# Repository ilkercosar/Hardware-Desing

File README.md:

# Future Hardware-Desing
- 4-6 layer mipi csi to serializer board
- Usb camera controler board
- Luckfox Pico RV1103 I/0 board

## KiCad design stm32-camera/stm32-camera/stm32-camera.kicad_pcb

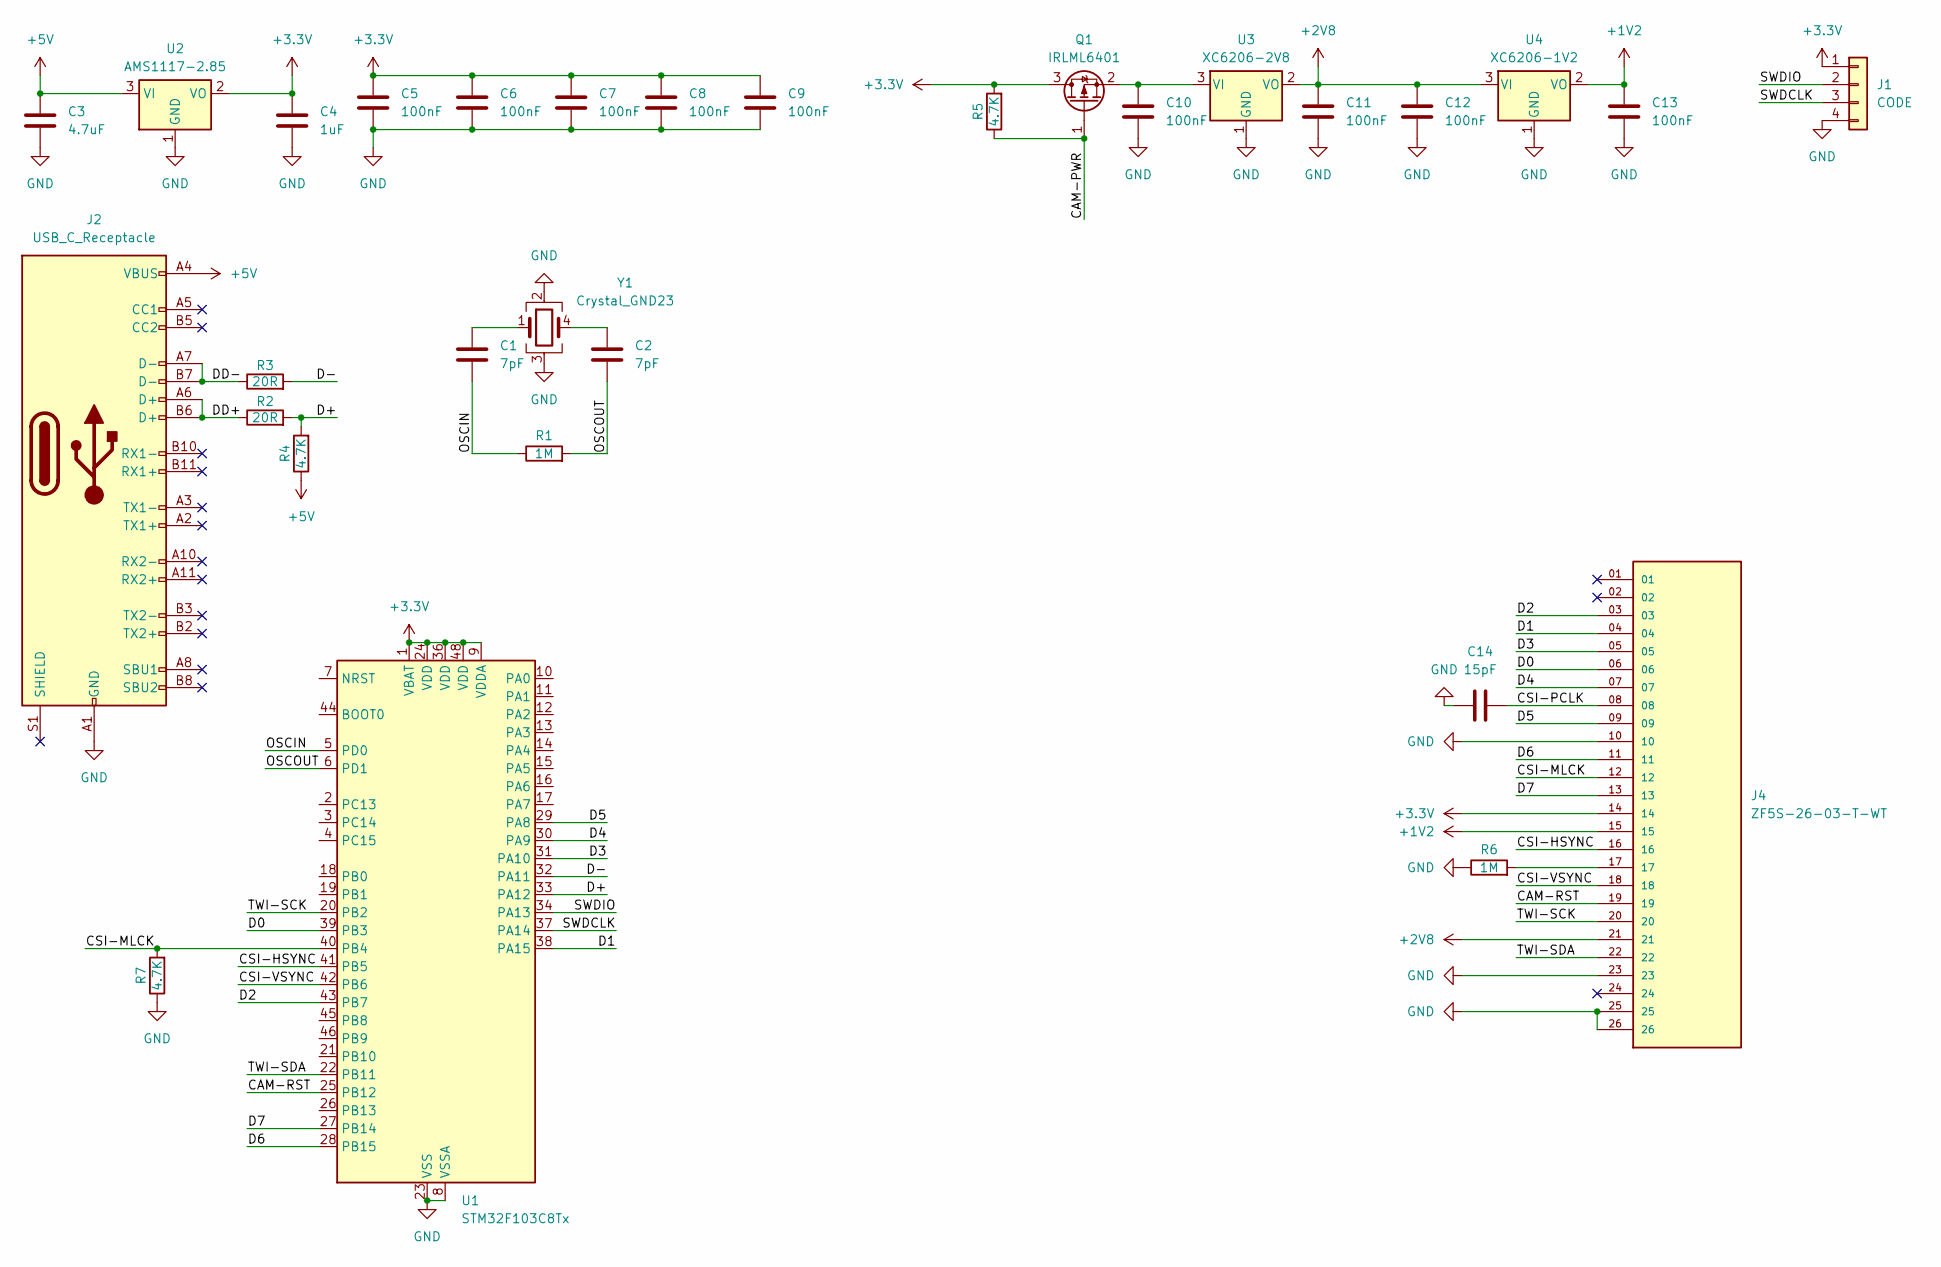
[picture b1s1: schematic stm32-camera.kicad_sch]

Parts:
C1, C2: 7pF; C_0402_1005Metric
C3: 4.7uF; C_0402_1005Metric
C4: 1uF; C_0402_1005Metric
C5, C6, C7, C8, C9, C10, C11, C12, C13: 100nF; C_0402_1005Metric
C14: 15pF; C_0402_1005Metric
J1: CODE; PinHeader_1x04_P2.54mm_Vertical
J2: USB_C_Receptacle; USB_C_Receptacle_JAE_DX07S024WJ3R400
J4: ZF5S-26-03-T-WT; SAMTEC_ZF5S-26-03-T-WT
Q1: IRLML6401; SOT-23
R1, R6: 1M; R_0402_1005Metric
R2, R3: 20R; R_0402_1005Metric
R4, R5, R7: 4.7K; R_0402_1005Metric
U1: STM32F103C8Tx; LQFP-48_7x7mm_P0.5mm
U2: AMS1117-2.85; SOT-223-3_TabPin2
U3: XC6206-2V8; SOT-23-3
U4: XC6206-1V2; SOT-23-3
Y1: Crystal_GND23; Crystal_SMD_SeikoEpson_FA128-4Pin_2.0x1.6mm

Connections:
+1V2: C13.1, J4.15, U4.2 (VO)
+2V8: C11.1, C12.1, J4.21, U3.2 (VO), U4.3 (VI)
+3.3V: C4.1, C5.1, C6.1, C7.1, C8.1, C9.1, J1.1, J4.14, Q1.3 (D), R5.2, U1.1 (VBAT), U1.9 (VDDA), U1.24 (VDD), U1.36 (VDD), U1.48 (VDD), U2.2 (VO)
+5V: C3.1, J2.A4 (VBUS), J2.A9 (VBUS), J2.B4 (VBUS), J2.B9 (VBUS), R4.1, U2.3 (VI)
/CAM-PWR: Q1.1 (G), R5.1
/CAM-RST: J4.19, U1.25 (PB12)
/CSI-HSYNC: J4.16, U1.41 (PB5)
/CSI-MLCK: J4.12, R7.2, U1.40 (PB4)
/CSI-PCLK: C14.2, J4.08
/CSI-VSYNC: J4.18, U1.42 (PB6)
/D0: J4.06, U1.39 (PB3)
/D1: J4.04, U1.38 (PA15)
/D2: J4.03, U1.43 (PB7)
/D3: J4.05, U1.31 (PA10)
/D4: J4.07, U1.30 (PA9)
/D5: J4.09, U1.29 (PA8)
/D6: J4.11, U1.28 (PB15)
/D7: J4.13, U1.27 (PB14)
/D+: R2.2, R4.2, U1.33 (PA12)
/D-: R3.2, U1.32 (PA11)
/DD+: J2.A6 (D+), J2.B6 (D+), R2.1
/DD-: J2.A7 (D-), J2.B7 (D-), R3.1
/OSCIN: C1.2, R1.1, U1.5 (PD0)
/OSCOUT: C2.2, R1.2, U1.6 (PD1)
/SWDCLK: J1.3, U1.37 (PA14)
/SWDIO: J1.2, U1.34 (PA13)
/TWI-SCK: J4.20, U1.20 (PB2)
/TWI-SDA: J4.22, U1.22 (PB11)
GND: C3.2, C4.2, C5.2, C6.2, C7.2, C8.2, C9.2, C10.2, C11.2, C12.2, C13.2, C14.1, J1.4, J2.A1 (GND), J2.A12 (GND), J2.B1 (GND), J2.B12 (GND), J4.10, J4.23, J4.25, J4.26, R6.1, R7.1, U1.8 (VSSA), U1.23 (VSS), U1.35 (VSS), U1.47 (VSS), U2.1 (GND), U3.1 (GND), U4.1 (GND), Y1.2, Y1.3
unnamed: C1.1, Y1.1
unnamed: C2.1, Y1.4
unnamed: J4.17, R6.2
unnamed: C10.1, Q1.2 (S), U3.3 (VI)

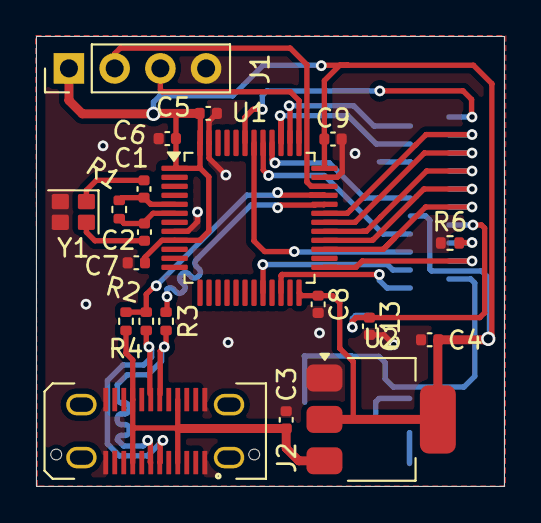
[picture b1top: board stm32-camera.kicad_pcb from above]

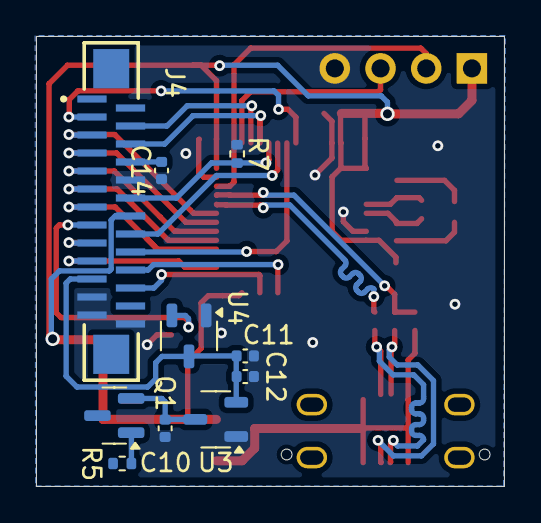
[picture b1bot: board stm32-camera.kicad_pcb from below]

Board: 2 copper layers, 26.0 x 25.0 mm, 30 parts (10 on the bottom side), 33 nets.

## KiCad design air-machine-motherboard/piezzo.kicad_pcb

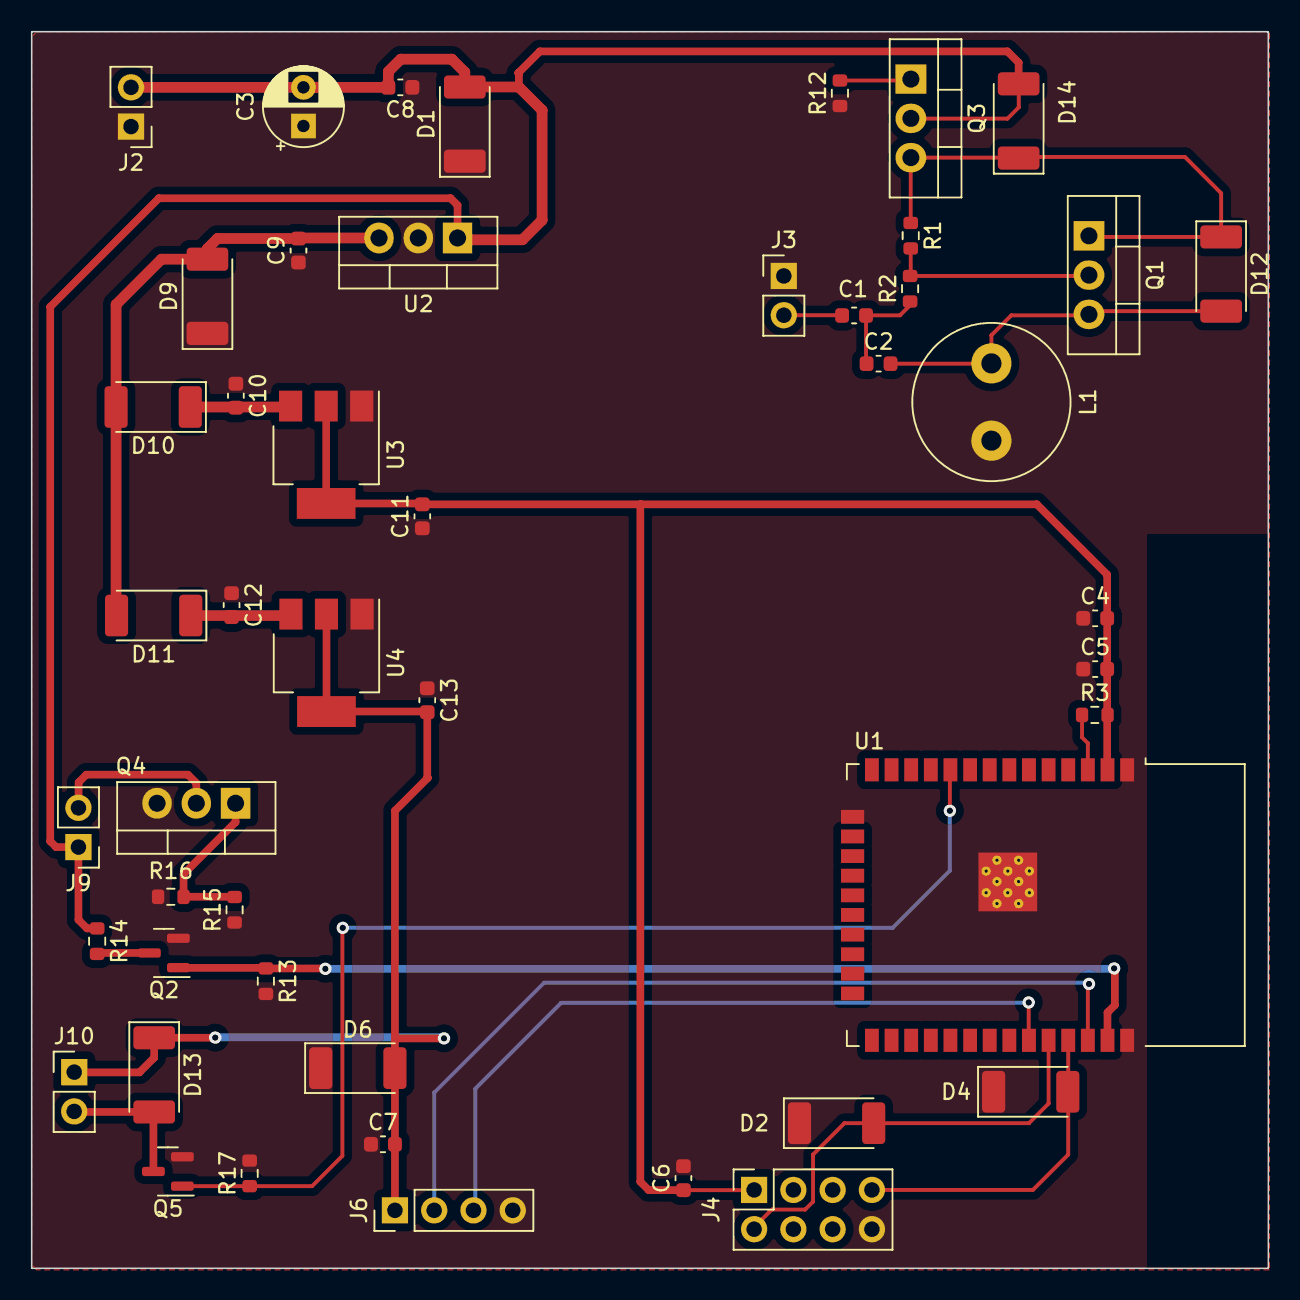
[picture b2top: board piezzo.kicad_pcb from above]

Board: 2 copper layers, 80.0 x 80.0 mm, 48 parts (0 on the bottom side), 24 nets.

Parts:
C1, C5: 1uF; C_0603_1608Metric
C2: 47uH; C_0603_1608Metric
C3: 47uH; CP_Radial_D5.0mm_P2.50mm
C4, C10, C12: 10uF; C_0603_1608Metric
C6, C7: 100nF; C_0603_1608Metric
C8, C9: 330nF; C_0603_1608Metric
C11, C13: 4.7uF; C_0603_1608Metric
D1, D9: SMBJ30CA; D_MELF
D2, D4, D6: SMAJ10CA; D_MELF
D10, D11: RS1M; D_MELF
D12, D13, D14: RS1A; D_MELF
J2, J3: OUT; PinHeader_1x02_P2.54mm_Vertical
J4: CODE; PinSocket_2x04_P2.54mm_Vertical
J6: LCD; PinHeader_1x04_P2.54mm_Vertical
J9: LED; PinHeader_1x02_P2.54mm_Vertical
J10: MOTOR; PinHeader_1x02_P2.54mm_Vertical
L1: 220uH; L_Radial_D10.0mm_P5.00mm_Fastron_07M
Q1: BU407; TO-220-3_Vertical
Q2, Q5: 2N7002; SOT-23
Q3: IRF9540N; TO-220-3_Vertical
Q4: IRF540N; TO-220-3_Vertical
R1, R2: 2.2K; R_0603_1608Metric
R3: 10K; R_0603_1608Metric
R12, R13, R16, R17: 47K; R_0603_1608Metric
R14: 4.7K; R_0603_1608Metric
R15: 1K; R_0603_1608Metric
U1: ESP32-WROOM-32D
U2: LM7812_TO220; TO-220-3_Vertical
U3, U4: AMS1117-3.3; SOT-223-3_TabPin2

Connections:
+3.3V: C4.2, C5.2, C6.1, C7.2, C11.2, C13.2, D6.2 (A2), D13.1 (K), J4.1, J6.1, J10.1, R3.2, U1.2 (VDD), U3.2 (VO), U4.2 (VO)
+12V: C9.2, D9.2 (A2), D10.2 (A), D11.2 (A), U2.3 (VO)
+24V: C3.2, C8.2, D1.2 (A2), D14.2 (A), J2.2, J9.1, Q3.2 (D), R14.1, U2.1 (VI)
/mcu-line/IO0: J4.4, U1.25 (IO0)
/mcu-line/RX: D2.2 (A2), J4.2, U1.34 (RXD0/IO3)
/mcu-line/TX: D4.2 (A2), J4.7, U1.35 (TXD0/IO1)
/piezzo-line/PIEZZO+: C1.2, J3.2
G: Q3.1 (G), R12.2, U1.28 (IO17)
GND: C3.1, C4.1, C5.1, C6.2, C7.1, C8.1, C9.1, C10.1, C11.1, C12.1, C13.1, D1.1 (A1), D2.1 (A1), D4.1 (A1), D6.1 (A1), D9.1 (A1), J2.1, J3.1, J4.8, J6.4, L1.2, Q2.2 (S), Q4.3 (S), Q5.2 (S), R12.1, R13.2, R15.1, R16.2, R17.2, U1.1 (GND), U1.15 (GND), U1.38 (GND), U1.39 (GND), U2.2 (GND), U3.1 (GND), U4.1 (GND)
LED: Q2.1 (G), R13.1, U1.37 (IO23)
MOTOR-SG: Q5.1 (G), R17.1, U1.10 (IO25)
unnamed: C1.1, C2.1, R2.1
unnamed: C10.2, D10.1 (K), U3.3 (VI)
unnamed: C12.2, D11.1 (K), U4.3 (VI)
unnamed: C2.2, D12.2 (A), L1.1, Q1.3 (E)
unnamed: D12.1 (K), D14.1 (K), Q1.1 (C), Q3.3 (S), R1.1
unnamed: D13.2 (A), J10.2, Q5.3 (D)
unnamed: J9.2, Q4.2 (D)
unnamed: Q1.2 (B), R1.2, R2.2
unnamed: Q2.3 (D), R14.2
unnamed: Q4.1 (G), R15.2, R16.1
unnamed: R3.1, U1.3 (EN)
SCL: J6.2, U1.36 (IO22)
SDA: J6.3, U1.33 (IO21)

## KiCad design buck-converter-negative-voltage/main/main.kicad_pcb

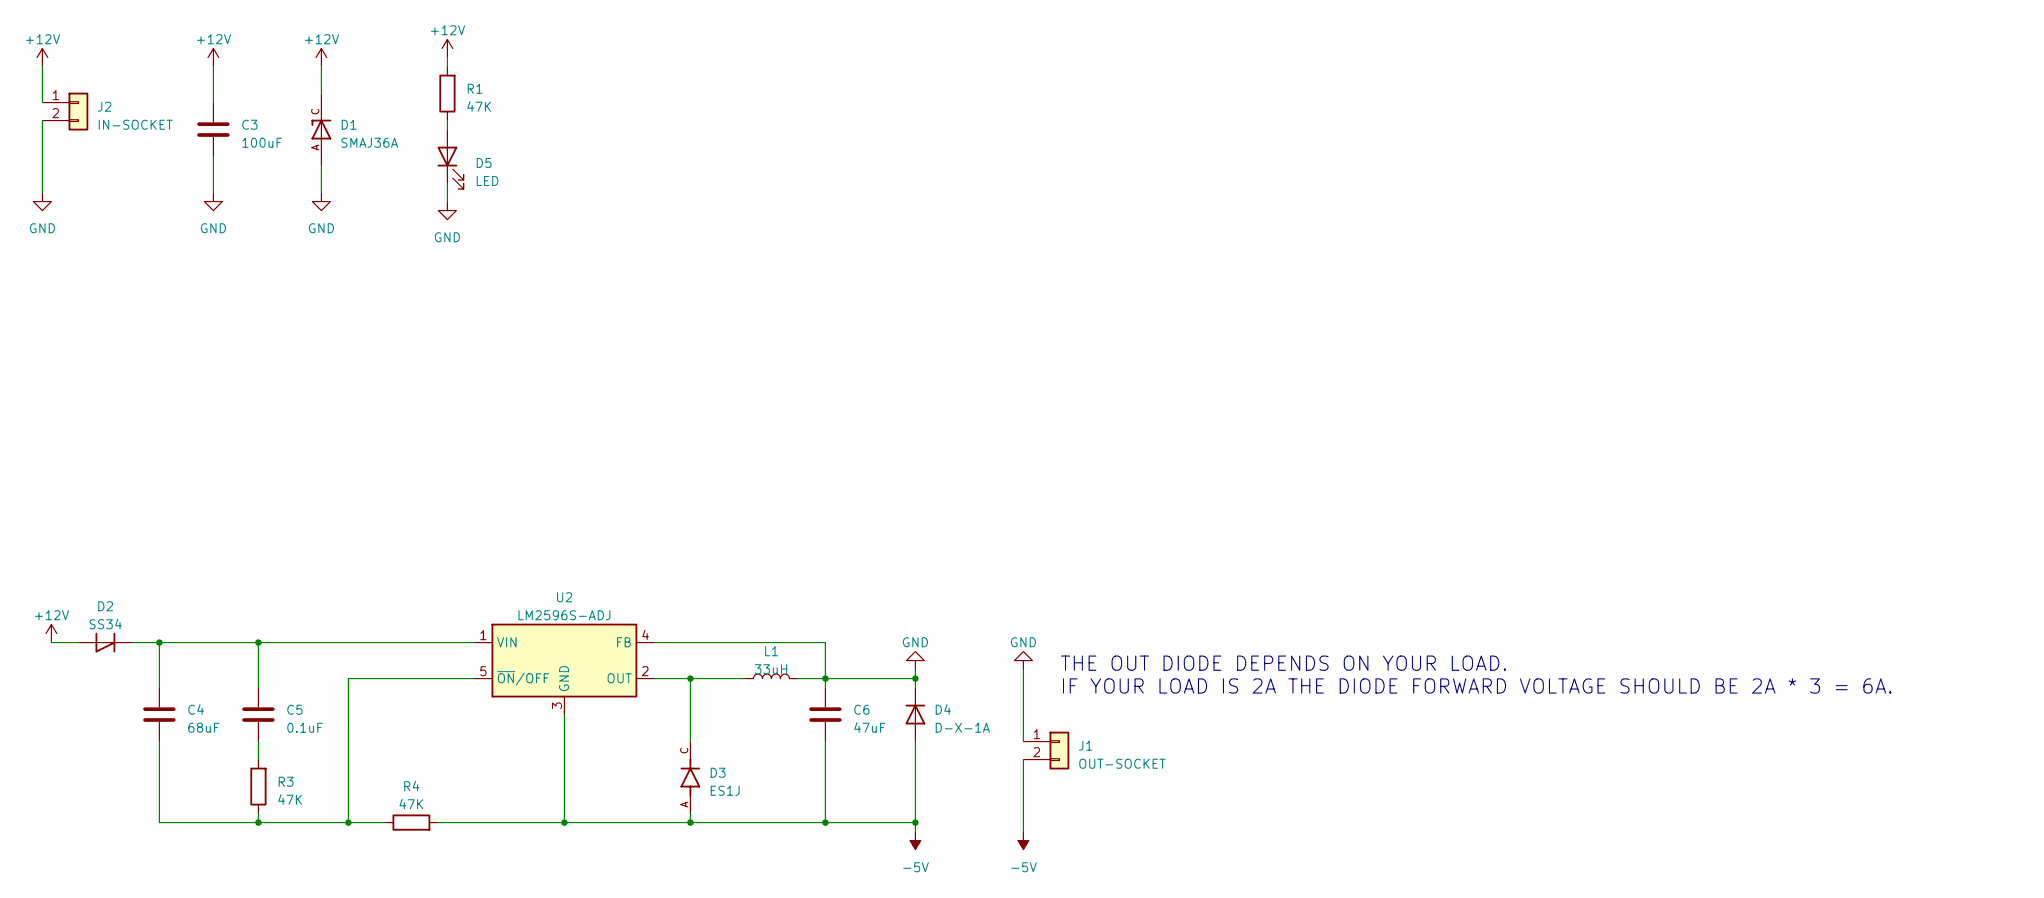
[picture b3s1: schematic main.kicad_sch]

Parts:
C3: 100uF; C_1210_3225Metric
C4: 68uF; CP_Radial_D5.0mm_P2.50mm
C5: 0.1uF; C_0603_1608Metric
C6: 47uF; C_1210_3225Metric
D1: SMAJ36A; DIOM4325X250N; PARTREV S2102
D2: SS34; D_SOD-123
D3: ES1J; DIOM4325X250N; PARTREV L2102
D4: D-X-1A; D_DO-15_P5.08mm_Vertical_AnodeUp
D5: LED; LED_0603_1608Metric
J1: OUT-SOCKET; PinHeader_1x02_P2.54mm_Vertical
J2: IN-SOCKET; PinHeader_1x02_P2.54mm_Vertical
L1: 33uH; L_Bourns_SRR1208_12.7x12.7mm
R1, R3, R4: 47K; R_0603_1608Metric
U2: LM2596S-ADJ; TO-263-5_TabPin3

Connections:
+12V: C3.1, D1.C, D2.2 (A), J2.1, R1.2
-5V: C6.2, D3.A, D4.2 (A), J1.2, R4.2, U2.3 (GND)
GND: C3.2, C6.1, D1.A, D4.1 (K), D5.1 (K), J1.1, J2.2, L1.2, U2.4 (FB)
unnamed: C5.2, R3.2
unnamed: C4.1, C5.1, D2.1 (K), U2.1 (VIN)
unnamed: D5.2 (A), R1.1
unnamed: D3.C, L1.1, U2.2 (OUT)
unnamed: C4.2, R3.1, R4.1, U2.5 (~ON/OFF)

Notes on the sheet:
THE OUT DIODE DEPENDS ON YOUR LOAD. IF YOUR LOAD IS 2A THE DIODE FORWARD VOLTAGE SHOULD BE 2A * 3 = 6A.

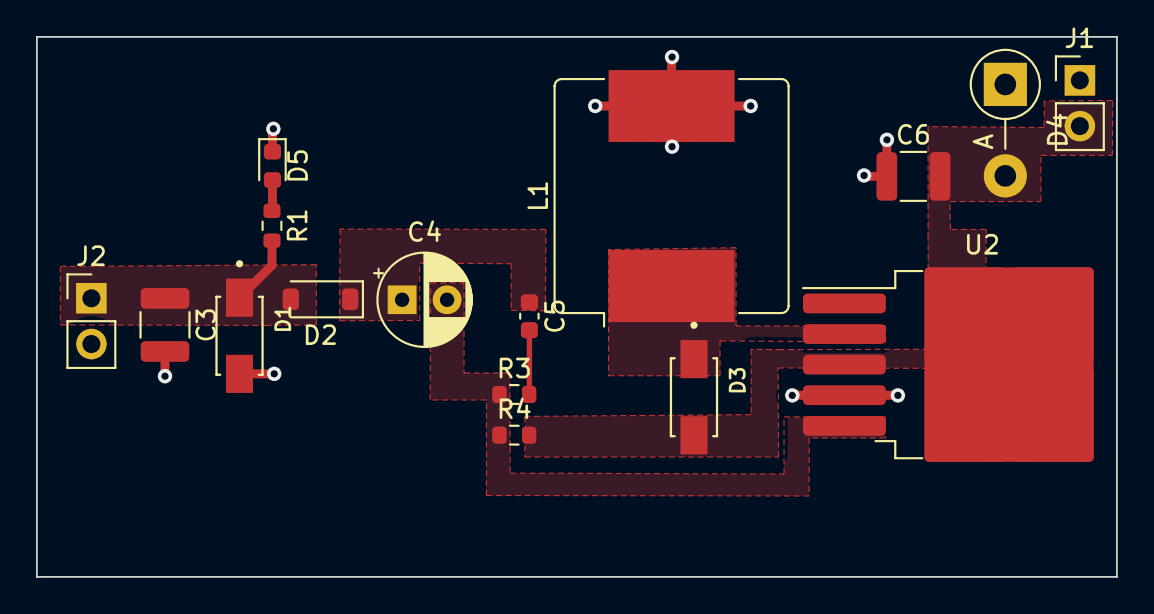
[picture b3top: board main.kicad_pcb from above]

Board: 4 copper layers, 60.0 x 30.0 mm, 16 parts (0 on the bottom side), 8 nets.

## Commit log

2023-07-15 BLDC-Motor-Driver
2023-07-15 Rocket-Flight-Control
2023-07-15 DC-Servo-Motor-Driver
2023-07-15 README.md
2023-08-25 4 layer buck converter desing
2024-07-07 only shematic
2024-07-15 wireles air machine motherboard
2024-11-26 STM32F103C8T6 camera application tiny module
